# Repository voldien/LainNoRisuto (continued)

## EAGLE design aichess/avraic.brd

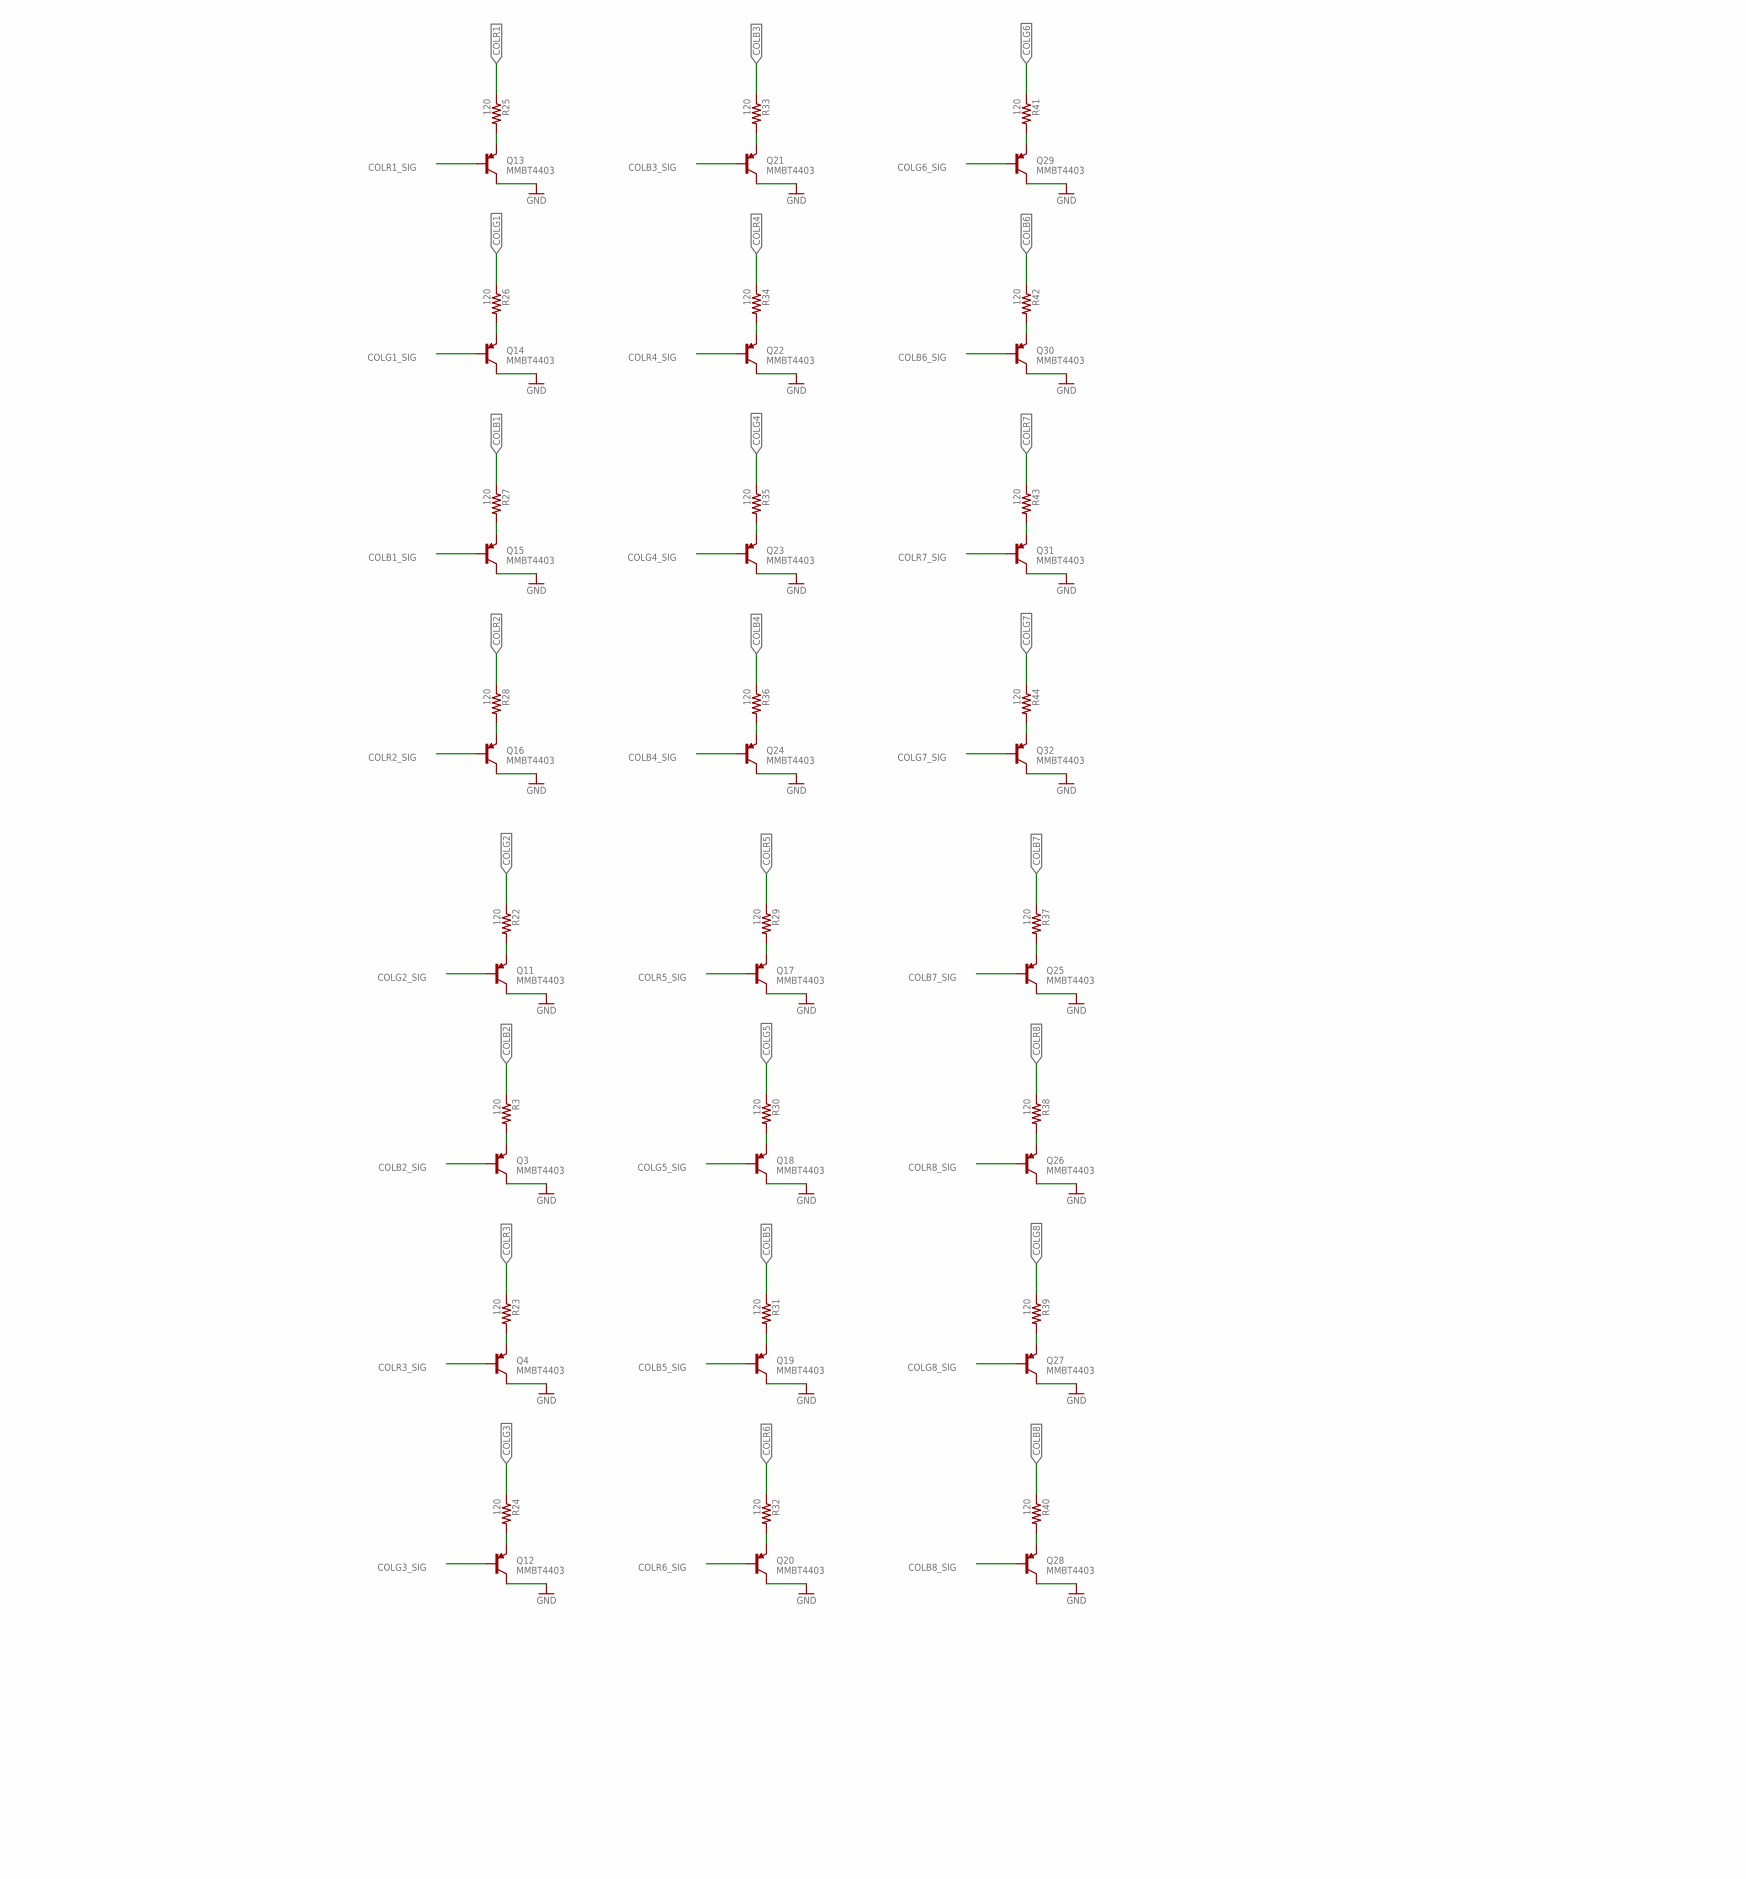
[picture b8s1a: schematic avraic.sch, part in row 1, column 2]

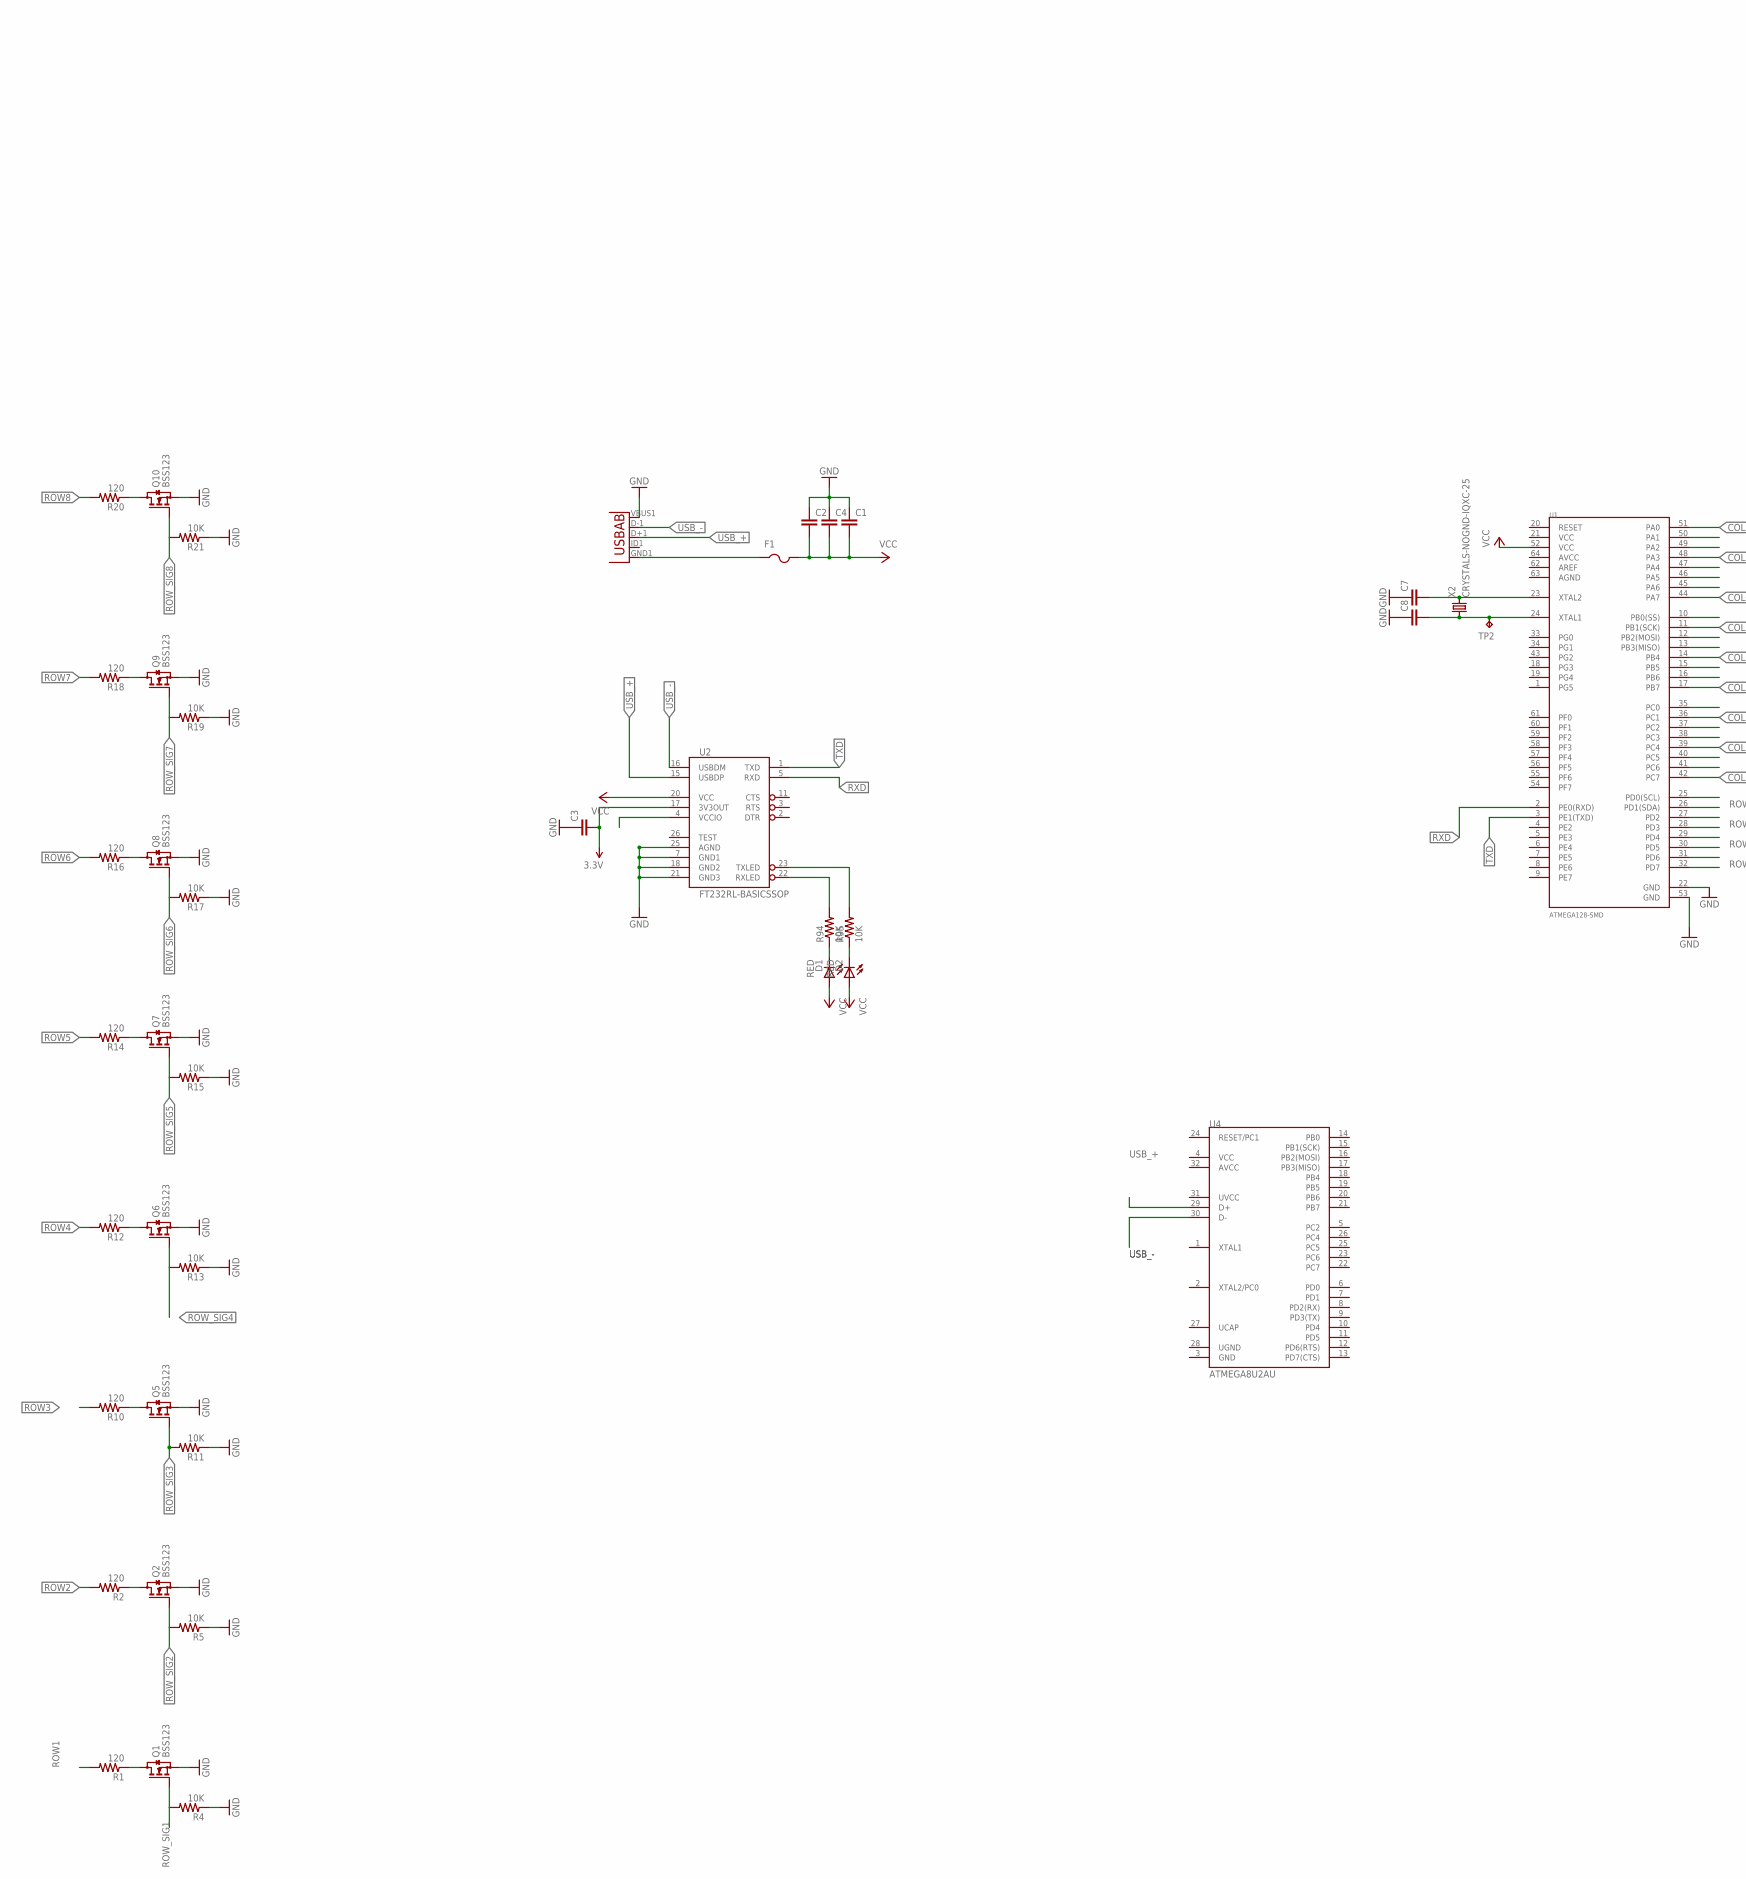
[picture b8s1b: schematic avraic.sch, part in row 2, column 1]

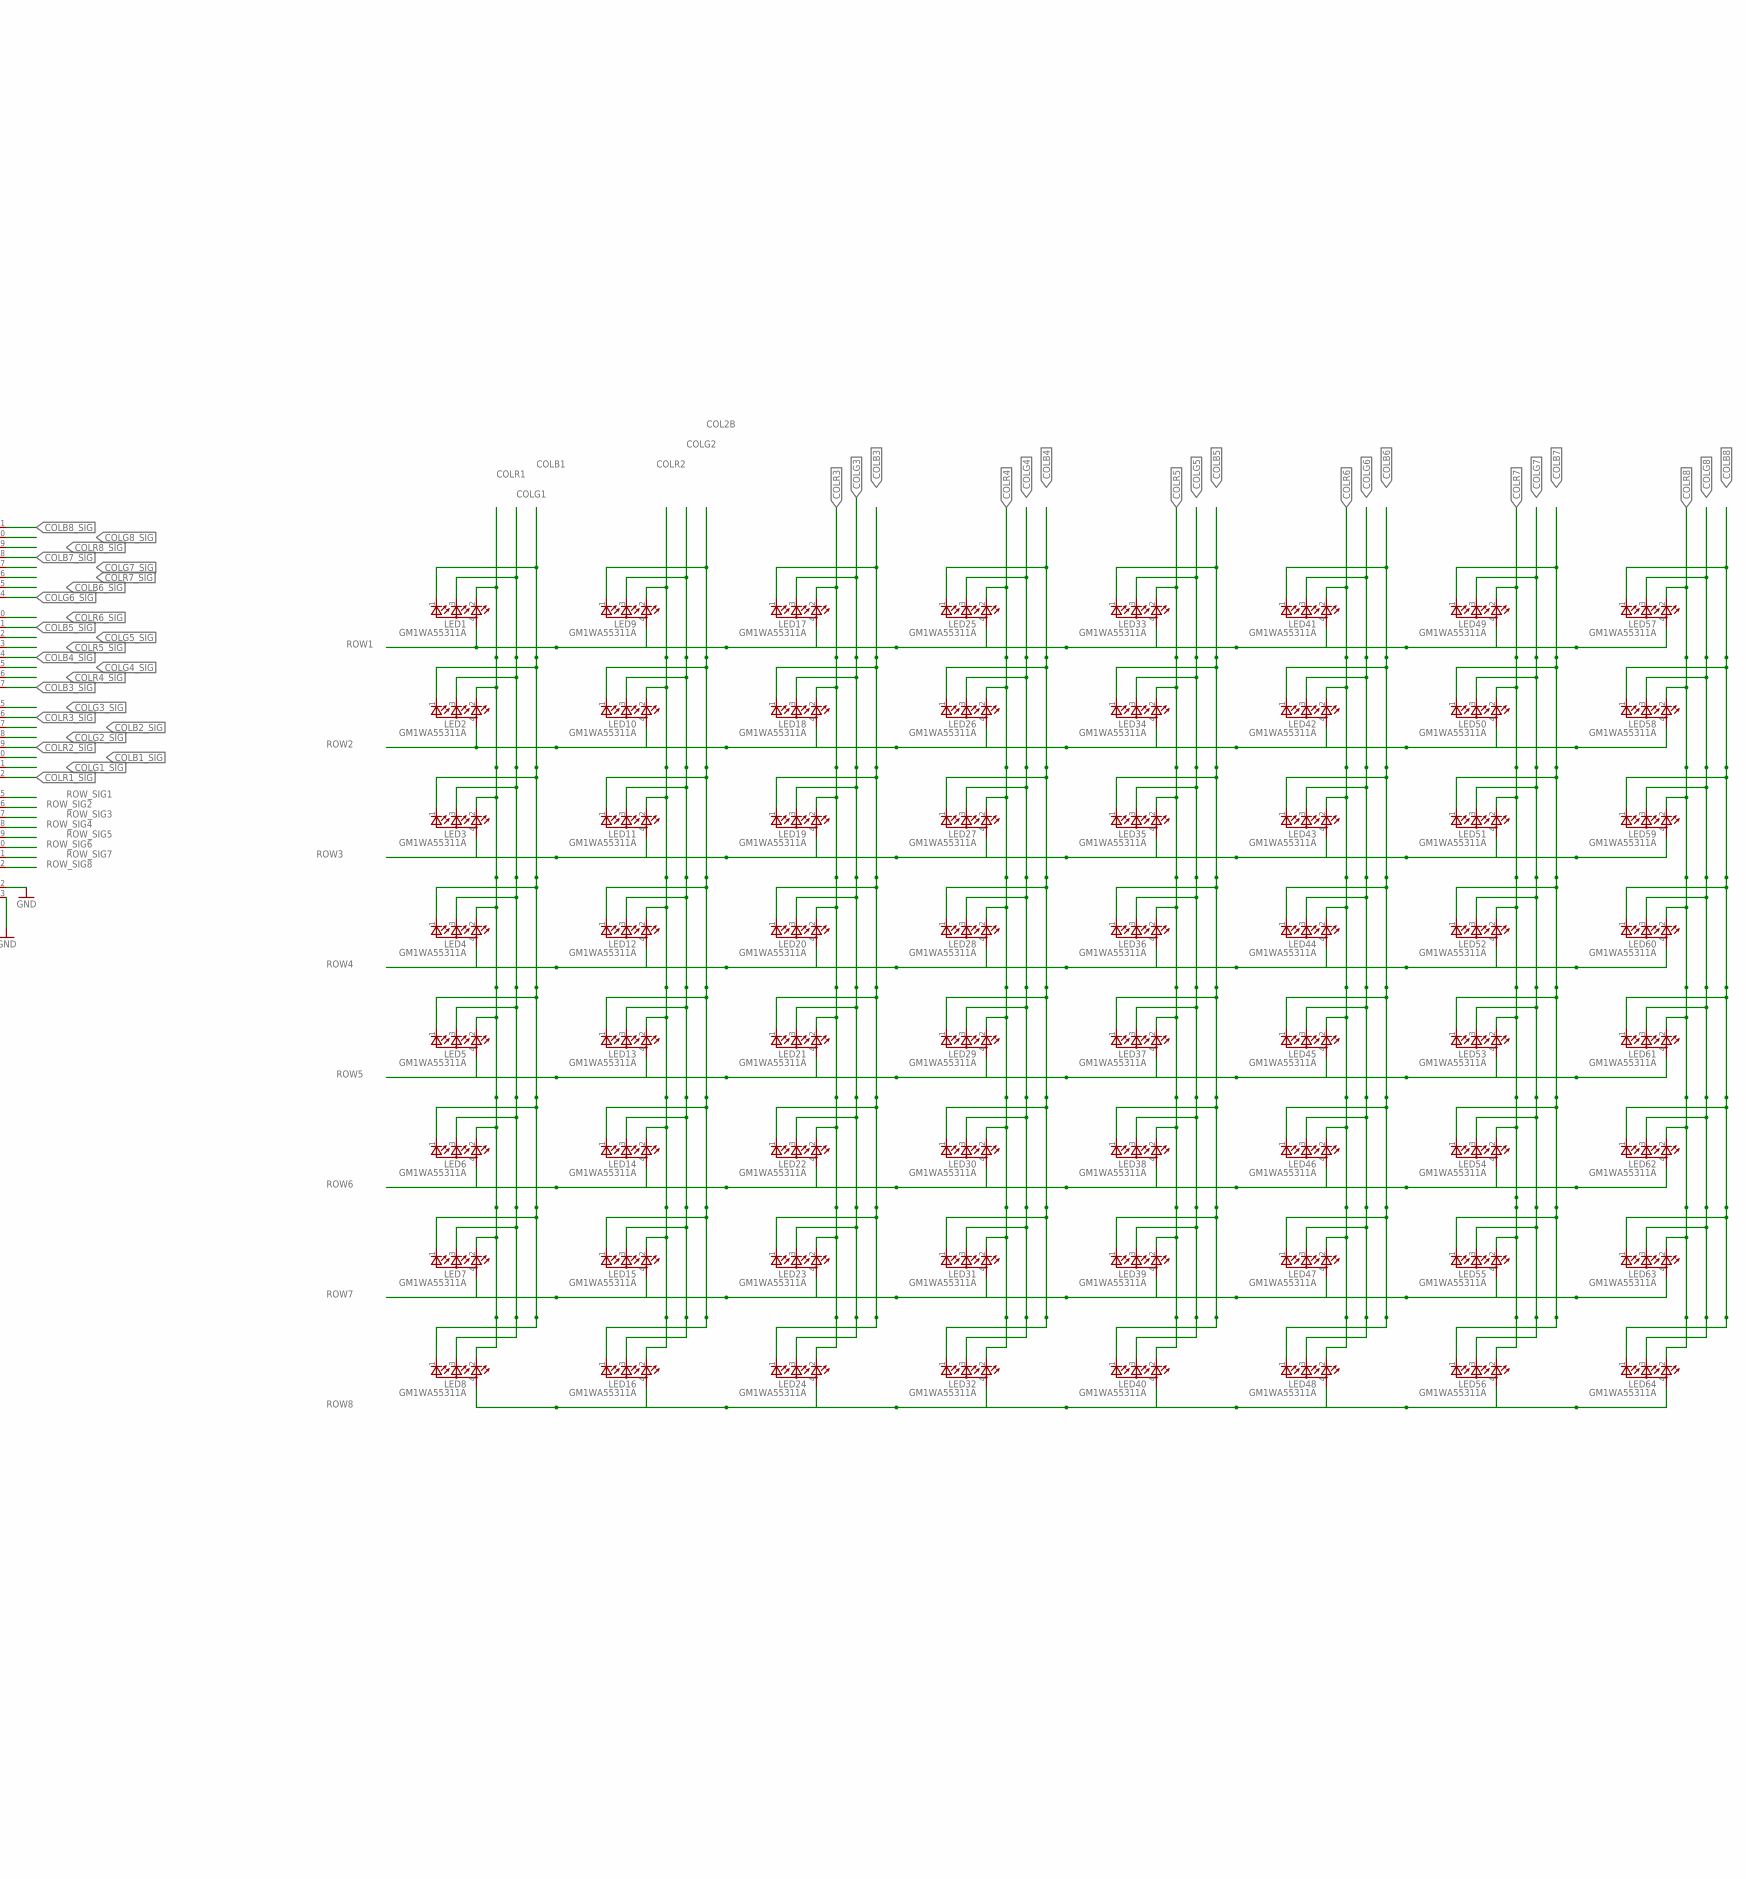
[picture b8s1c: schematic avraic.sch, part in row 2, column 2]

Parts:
C1, C2, C4: C-EUC0201; C0201
C3, C7, C8: C-EUC0402K; C0402K
D1, D2: RED; CHIP-LED0603
F1: PTCFUSE-1206; R1206
LED1, LED2, LED3, LED4, LED5, LED6, LED7, LED8, LED9, LED10, LED11, LED12, LED13, LED14, LED15, LED16, LED17, LED18, LED19, LED20, LED21, LED22, LED23, LED24, LED25, LED26, LED27, LED28, LED29, LED30, LED31, LED32, LED33, LED34, LED35, LED36, LED37, LED38, LED39, LED40, LED41, LED42, LED43, LED44, LED45, LED46, LED47, LED48, LED49, LED50, LED51, LED52, LED53, LED54, LED55, LED56, LED57, LED58, LED59, LED60, LED61, LED62, LED63, LED64: GM1WA55311A
Q1, Q2, Q5, Q6, Q7, Q8, Q9, Q10: BSS123; SOT23
Q3, Q4, Q11, Q12, Q13, Q14, Q15, Q16, Q17, Q18, Q19, Q20, Q21, Q22, Q23, Q24, Q25, Q26, Q27, Q28, Q29, Q30, Q31, Q32: MMBT4403; SOT23-3
R1, R2, R10, R12, R14, R16, R18, R20, R24, R25, R30, R31, R32: 120; 0603-RES
R3, R22, R23, R26, R27, R28, R29, R33, R34, R35, R36, R37, R38, R39, R40, R41, R42, R43, R44: 120; MINI_MELF-0102R
R4, R5, R11, R13, R15, R17, R19, R21, R94, R95: 10K; 0603-RES
TP2: TPB1,27; B1,27
U1: ATMEGA128-SMD; TQFP64_14X14MM
U2: FT232RL-BASICSSOP; SSOP28DB
U3: USB""; USB-MICRO-SMD
U4: ATMEGA8U2AU; TQFP32-08
X2: CRYSTALS-NOGND-IQXC-25; 2.0X1.2-2PAD

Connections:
3.3V: C3.2, U2.17 (3V3OUT)
COL2B: LED9.1 (CGREEN), LED10.1 (CGREEN), LED11.1 (CGREEN), LED12.1 (CGREEN), LED13.1 (CGREEN), LED14.1 (CGREEN), LED15.1 (CGREEN), LED16.1 (CGREEN)
COLB1: LED1.1 (CGREEN), LED2.1 (CGREEN), LED3.1 (CGREEN), LED4.1 (CGREEN), LED5.1 (CGREEN), LED6.1 (CGREEN), LED7.1 (CGREEN), LED8.1 (CGREEN), R27.1
COLB1_SIG: Q15.1 (B), U1.40 (PC5)
COLB2: R3.1
COLB2_SIG: Q3.1 (B), U1.37 (PC2)
COLB3: LED17.1 (CGREEN), LED18.1 (CGREEN), LED19.1 (CGREEN), LED20.1 (CGREEN), LED21.1 (CGREEN), LED22.1 (CGREEN), LED23.1 (CGREEN), LED24.1 (CGREEN), R33.1
COLB3_SIG: Q21.1 (B), U1.17 (PB7)
COLB4: LED25.1 (CGREEN), LED26.1 (CGREEN), LED27.1 (CGREEN), LED28.1 (CGREEN), LED29.1 (CGREEN), LED30.1 (CGREEN), LED31.1 (CGREEN), LED32.1 (CGREEN), R36.1
COLB4_SIG: Q24.1 (B), U1.14 (PB4)
COLB5: LED33.1 (CGREEN), LED34.1 (CGREEN), LED35.1 (CGREEN), LED36.1 (CGREEN), LED37.1 (CGREEN), LED38.1 (CGREEN), LED39.1 (CGREEN), LED40.1 (CGREEN), R31.1
COLB5_SIG: Q19.1 (B), U1.11 (PB1(SCK))
COLB6: LED41.1 (CGREEN), LED42.1 (CGREEN), LED43.1 (CGREEN), LED44.1 (CGREEN), LED45.1 (CGREEN), LED46.1 (CGREEN), LED47.1 (CGREEN), LED48.1 (CGREEN), R42.1
COLB6_SIG: Q30.1 (B), U1.45 (PA6)
COLB7: LED49.1 (CGREEN), LED50.1 (CGREEN), LED51.1 (CGREEN), LED52.1 (CGREEN), LED53.1 (CGREEN), LED54.1 (CGREEN), LED55.1 (CGREEN), LED56.1 (CGREEN), R37.1
COLB7_SIG: Q25.1 (B), U1.48 (PA3)
COLB8: LED57.1 (CGREEN), LED58.1 (CGREEN), LED59.1 (CGREEN), LED60.1 (CGREEN), LED61.1 (CGREEN), LED62.1 (CGREEN), LED63.1 (CGREEN), LED64.1 (CGREEN), R40.1
COLB8_SIG: Q28.1 (B), U1.51 (PA0)
COLG1: LED1.3 (CBLUE), LED2.3 (CBLUE), LED3.3 (CBLUE), LED4.3 (CBLUE), LED5.3 (CBLUE), LED6.3 (CBLUE), LED7.3 (CBLUE), LED8.3 (CBLUE), R26.1
COLG1_SIG: Q14.1 (B), U1.41 (PC6)
COLG2: LED9.3 (CBLUE), LED10.3 (CBLUE), LED11.3 (CBLUE), LED12.3 (CBLUE), LED13.3 (CBLUE), LED14.3 (CBLUE), LED15.3 (CBLUE), LED16.3 (CBLUE), R22.1
COLG2_SIG: Q11.1 (B), U1.38 (PC3)
COLG3: LED17.3 (CBLUE), LED18.3 (CBLUE), LED19.3 (CBLUE), LED20.3 (CBLUE), LED21.3 (CBLUE), LED22.3 (CBLUE), LED23.3 (CBLUE), LED24.3 (CBLUE), R24.1
COLG3_SIG: Q12.1 (B), U1.35 (PC0)
COLG4: LED25.3 (CBLUE), LED26.3 (CBLUE), LED27.3 (CBLUE), LED28.3 (CBLUE), LED29.3 (CBLUE), LED30.3 (CBLUE), LED31.3 (CBLUE), LED32.3 (CBLUE), R35.1
COLG4_SIG: Q23.1 (B), U1.15 (PB5)
COLG5: LED33.3 (CBLUE), LED34.3 (CBLUE), LED35.3 (CBLUE), LED36.3 (CBLUE), LED37.3 (CBLUE), LED38.3 (CBLUE), LED39.3 (CBLUE), LED40.3 (CBLUE), R30.1
COLG5_SIG: Q18.1 (B), U1.12 (PB2(MOSI))
COLG6: LED41.3 (CBLUE), LED42.3 (CBLUE), LED43.3 (CBLUE), LED44.3 (CBLUE), LED45.3 (CBLUE), LED46.3 (CBLUE), LED47.3 (CBLUE), LED48.3 (CBLUE), R41.1
COLG6_SIG: Q29.1 (B), U1.44 (PA7)
COLG7: LED49.3 (CBLUE), LED50.3 (CBLUE), LED51.3 (CBLUE), LED52.3 (CBLUE), LED53.3 (CBLUE), LED54.3 (CBLUE), LED55.3 (CBLUE), LED56.3 (CBLUE), R44.1
COLG7_SIG: Q32.1 (B), U1.47 (PA4)
COLG8: LED57.3 (CBLUE), LED58.3 (CBLUE), LED59.3 (CBLUE), LED60.3 (CBLUE), LED61.3 (CBLUE), LED62.3 (CBLUE), LED63.3 (CBLUE), LED64.3 (CBLUE), R39.1
COLG8_SIG: Q27.1 (B), U1.50 (PA1)
COLR1: LED1.2 (CRED), LED2.2 (CRED), LED3.2 (CRED), LED4.2 (CRED), LED5.2 (CRED), LED6.2 (CRED), LED7.2 (CRED), LED8.2 (CRED), R25.1
COLR1_SIG: Q13.1 (B), U1.42 (PC7)
COLR2: LED9.2 (CRED), LED10.2 (CRED), LED11.2 (CRED), LED12.2 (CRED), LED13.2 (CRED), LED14.2 (CRED), LED15.2 (CRED), LED16.2 (CRED), R28.1
COLR2_SIG: Q16.1 (B), U1.39 (PC4)
COLR3: LED17.2 (CRED), LED18.2 (CRED), LED19.2 (CRED), LED20.2 (CRED), LED21.2 (CRED), LED22.2 (CRED), LED23.2 (CRED), LED24.2 (CRED), R23.1
COLR3_SIG: Q4.1 (B), U1.36 (PC1)
COLR4: LED25.2 (CRED), LED26.2 (CRED), LED27.2 (CRED), LED28.2 (CRED), LED29.2 (CRED), LED30.2 (CRED), LED31.2 (CRED), LED32.2 (CRED), R34.1
COLR4_SIG: Q22.1 (B), U1.16 (PB6)
COLR5: LED33.2 (CRED), LED34.2 (CRED), LED35.2 (CRED), LED36.2 (CRED), LED37.2 (CRED), LED38.2 (CRED), LED39.2 (CRED), LED40.2 (CRED), R29.1
COLR5_SIG: Q17.1 (B), U1.13 (PB3(MISO))
COLR6: LED41.2 (CRED), LED42.2 (CRED), LED43.2 (CRED), LED44.2 (CRED), LED45.2 (CRED), LED46.2 (CRED), LED47.2 (CRED), LED48.2 (CRED), R32.1
COLR6_SIG: Q20.1 (B), U1.10 (PB0(SS))
COLR7: LED49.2 (CRED), LED50.2 (CRED), LED51.2 (CRED), LED52.2 (CRED), LED53.2 (CRED), LED54.2 (CRED), LED55.2 (CRED), LED56.2 (CRED), R43.1
COLR7_SIG: Q31.1 (B), U1.46 (PA5)
COLR8: LED57.2 (CRED), LED58.2 (CRED), LED59.2 (CRED), LED60.2 (CRED), LED61.2 (CRED), LED62.2 (CRED), LED63.2 (CRED), LED64.2 (CRED), R38.1
COLR8_SIG: Q26.1 (B), U1.49 (PA2)
GND: C1.1, C2.1, C3.1, C4.1, C7.1, C8.1, Q1.2 (S), Q2.2 (S), Q3.3 (C), Q4.3 (C), Q5.2 (S), Q6.2 (S), Q7.2 (S), Q8.2 (S), Q9.2 (S), Q10.2 (S), Q11.3 (C), Q12.3 (C), Q13.3 (C), Q14.3 (C), Q15.3 (C), Q16.3 (C), Q17.3 (C), Q18.3 (C), Q19.3 (C), Q20.3 (C), Q21.3 (C), Q22.3 (C), Q23.3 (C), Q24.3 (C), Q25.3 (C), Q26.3 (C), Q27.3 (C), Q28.3 (C), Q29.3 (C), Q30.3 (C), Q31.3 (C), Q32.3 (C), R4.1, R5.1, R11.1, R13.1, R15.1, R17.1, R19.1, R21.1, U1.22 (GND), U1.53 (GND), U2.7 (GND1), U2.18 (GND2), U2.21 (GND3), U2.25 (AGND), U3.VBUS1 (VBUS)
unnamed: F1.1, U3.GND1 (GND)
unnamed: Q11.2 (E), R22.2
unnamed: Q1.3 (D), R1.1
unnamed: Q3.2 (E), R3.2
unnamed: Q4.2 (E), R23.2
unnamed: Q2.3 (D), R2.1
unnamed: D1.C, R94.1
unnamed: Q12.2 (E), R24.2
unnamed: D2.C, R95.1
unnamed: C7.2, U1.23 (XTAL2), X2.2
unnamed: C8.2, TP2.TP, U1.24 (XTAL1), X2.1
unnamed: Q13.2 (E), R25.2
unnamed: Q14.2 (E), R26.2
unnamed: Q15.2 (E), R27.2
unnamed: Q16.2 (E), R28.2
unnamed: Q17.2 (E), R29.2
unnamed: Q18.2 (E), R30.2
unnamed: Q19.2 (E), R31.2
unnamed: Q20.2 (E), R32.2
unnamed: Q21.2 (E), R33.2
unnamed: Q22.2 (E), R34.2
unnamed: Q23.2 (E), R35.2
unnamed: Q24.2 (E), R36.2
unnamed: Q25.2 (E), R37.2
unnamed: Q26.2 (E), R38.2
unnamed: Q27.2 (E), R39.2
unnamed: Q28.2 (E), R40.2
unnamed: Q29.2 (E), R41.2
unnamed: Q30.2 (E), R42.2
unnamed: Q31.2 (E), R43.2
unnamed: Q32.2 (E), R44.2
unnamed: Q5.3 (D), R10.1
unnamed: Q6.3 (D), R12.1
unnamed: Q7.3 (D), R14.1
unnamed: Q8.3 (D), R16.1
unnamed: Q9.3 (D), R18.1
unnamed: Q10.3 (D), R20.1
unnamed: R95.2, U2.23 (TXLED)
unnamed: R94.2, U2.22 (RXLED)
ROW1: LED1.4 (A), LED9.4 (A), LED17.4 (A), LED25.4 (A), LED33.4 (A), LED41.4 (A), LED49.4 (A), LED57.4 (A), R1.2
ROW2: LED2.4 (A), LED10.4 (A), LED18.4 (A), LED26.4 (A), LED34.4 (A), LED42.4 (A), LED50.4 (A), LED58.4 (A), R2.2
ROW3: LED3.4 (A), LED11.4 (A), LED19.4 (A), LED27.4 (A), LED35.4 (A), LED43.4 (A), LED51.4 (A), LED59.4 (A), R10.2
ROW4: LED4.4 (A), LED12.4 (A), LED20.4 (A), LED28.4 (A), LED36.4 (A), LED44.4 (A), LED52.4 (A), LED60.4 (A), R12.2
ROW5: LED5.4 (A), LED13.4 (A), LED21.4 (A), LED29.4 (A), LED37.4 (A), LED45.4 (A), LED53.4 (A), LED61.4 (A), R14.2
ROW6: LED6.4 (A), LED14.4 (A), LED22.4 (A), LED30.4 (A), LED38.4 (A), LED46.4 (A), LED54.4 (A), LED62.4 (A), R16.2
ROW7: LED7.4 (A), LED15.4 (A), LED23.4 (A), LED31.4 (A), LED39.4 (A), LED47.4 (A), LED55.4 (A), LED63.4 (A), R18.2
ROW8: LED8.4 (A), LED16.4 (A), LED24.4 (A), LED32.4 (A), LED40.4 (A), LED48.4 (A), LED56.4 (A), LED64.4 (A), R20.2
ROW_SIG1: Q1.1 (G), R4.2, U1.25 (PD0(SCL))
ROW_SIG2: Q2.1 (G), R5.2, U1.26 (PD1(SDA))
ROW_SIG3: Q5.1 (G), R11.2, U1.27 (PD2)
ROW_SIG4: Q6.1 (G), R13.2, U1.28 (PD3)
ROW_SIG5: Q7.1 (G), R15.2, U1.29 (PD4)
ROW_SIG6: Q8.1 (G), R17.2, U1.30 (PD5)
ROW_SIG7: Q9.1 (G), R19.2, U1.31 (PD6)
ROW_SIG8: Q10.1 (G), R21.2, U1.32 (PD7)
RXD: U1.2 (PE0(RXD)), U2.5 (RXD)
TXD: U1.3 (PE1(TXD)), U2.1 (TXD)
USB_+: U2.15 (USBDP), U3.D+1 (D+), U4.29 (D+)
USB_-: U2.16 (USBDM), U3.D-1 (D-), U4.30 (D-)
VCC: C1.2, C2.2, C4.2, D1.A, D2.A, F1.2, U1.52 (VCC), U2.20 (VCC)

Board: 2 copper layers, 153 parts (56 on the bottom side), 110 nets, no tracks yet.

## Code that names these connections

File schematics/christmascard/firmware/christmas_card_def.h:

#ifndef _CHRISTMAS_CARD_DEF_H_
#define _CHRISTMAS_CARD_DEF_H_ 1

/**
 * Push Button Registers and Pin.
 * Reset Button
 */
#define PUSH_BUTTON0_REG PORTB
#define PUSH_BUTTON0_DREG DDRB
#define PUSH_BUTTON0_IREG PINB
#define PUSH_BUTTON0_PIN PB0

/**
 * Push Button Registers and Pin
 * Next Button
 */
#define PUSH_BUTTON1_REG PORTA
#define PUSH_BUTTON1_DREG DDRA
#define PUSH_BUTTON1_IREG PINA
#define PUSH_BUTTON1_PIN PA1

/**
 * Shift Registers Output Enabled (SNx4HC595)
 * Pin and Registers.
 */
#define SHIFT_OE_REG PORTA /*		*/
#define SHIFT_OE_DREG DDRA /*		*/
#define SHIFT_OE_PIN PA0   /*		*/
#define SHIFT_OE_PWM_REG OCR0A

/**
 * Shift Register Shift Clock Pin (SNx4HC595)
 * and Registers  (RCLK)
 */
#define SHIFT_RCLK_REG PORTB /*	 	*/
#define SHIFT_RCLK_DREG DDRB /*	 	*/
#define SHIFT_RCLK_PIN PB1	 /*	 	*/

/**
 * Shift Registers Serial Data Pin (SNx4HC595)
 * and Registers
 */
#define SHIFT_DIO_REG PORTB /*		*/
#define SHIFT_DIO_DREG DDRB /*		*/
#define SHIFT_DIO_PIN PB2	/*		*/

/**
 * Shift Registers Latch (Flush Data to Output) Pin (SNx4HC595)
 * and Register  (SRCLR)
 */
#define SHIFT_LATCH_REG PORTB
#define SHIFT_LATCH_DREG DDRB
#define SHIFT_LATCH_PIN PB3 /*	Shift clock.	*/

/**
 *
 */
#define WS2811_DREG DDRA
#define WS2811_REG PORTA
#define WS2811_PIN PA3

#define WS2811_IN (1 << WS2811_PIN)

#endif

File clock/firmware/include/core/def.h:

/**

    Copyright (C) 2018  Valdemar Lindberg

    This program is free software: you can redistribute it and/or modify
    it under the terms of the GNU General Public License as published by
    the Free Software Foundation, either version 3 of the License, or
    (at your option) any later version.

    This program is distributed in the hope that it will be useful,
    but WITHOUT ANY WARRANTY; without even the implied warranty of
    MERCHANTABILITY or FITNESS FOR A PARTICULAR PURPOSE.  See the
    GNU General Public License for more details.

    You should have received a copy of the GNU General Public License
    along with this program.  If not, see <http://www.gnu.org/licenses/>.

*/
#ifndef _AVR_CLOCK_DEF_H_
#define _AVR_CLOCK_DEF_H_ 1
#include<avr/io.h>

/*	Set default frequency.	*/
#ifndef F_SCL
	#define F_SCL 100000UL /* SCL frequency	*/
#endif

/*	Set default baud rate.	*/
#ifndef BAUD
	#define BAUD 9600
#endif

#if defined(__AVR_ATmega328P__)
	#define SPIPORTS ( 1<<PD0) | (1 << PD1);
	#define I2CPORTS (1<<PD0) | (1 << PD1);
	#define UARTPORTS (1 << PD0) | (1 << PD1);
	#define BUTTONPORTS (1<<PD0) | (1 << PD1);
	#define pinclk PB0
	#define pindio PB1
	#define DIOPIN PINB
	#define DIODDR DDRB
	#define DIOPORT PORTB
#endif

#endif

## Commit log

2021-05-01 Config files
2021-05-01 Added tiny blink init source code
2021-05-01 Added init christmas card source code
2021-05-01 Added christmas schematic and pcb board
2021-05-01 Added atdb
2021-05-01 atdb pcb and schematic
2021-05-01 Added schematic and board
2021-05-01 Added root cmake
2021-05-01 Added
2021-05-01 Added readme and license file
2021-05-01 Add more source files
2021-05-01 Addded cmake module for handle avr-gcc with CMake
2021-05-01 Added gerber files
2021-05-01 Added schematic and board layout
2021-05-01 Added image of atdb
2021-05-02 Added layout
2021-05-03 Clock init souce files
2021-05-03 init source files
2021-05-12 Added board layout
2021-05-12 Minor update
2021-05-12 Init readme
2021-08-14 Minor
2021-08-31 Added init LED matrix
2021-09-01 Updated schematic
2021-09-03 Improved annotations and board layout
2021-09-04 Updated layout
2021-09-04 Updated layout grid
2021-09-04 Setup LED matrix
2021-09-05 Updated schematic and layout
2021-09-17 Updated minor
2021-12-22 Init
2022-01-06 Improved layout and schematic
2022-01-06 Init game console design
2022-04-12 Code formated
2023-01-20 Added init christmas card version 2.0
2023-04-06 Added init christmas card version 2 schematic and layout
2023-04-06 removed, replaced
2023-04-06 Added init source code, copied from the christmas card V1
2023-04-06 Added init source code for LED Clock matrix
2023-04-07 Added readme and removed file
2023-05-29 Added kicad git ignore
2023-05-29 Added init kicad source files
2023-05-29 Added init WIP game console firmware code
2023-05-30 Minor improvements
2025-05-21 Improved logic and other changes
2025-05-21 Updated git ignore
2025-05-21 Added AVR cmake config file
2025-05-21 Improved signal and other minor improvements
2025-05-22 Added pin interrupt, timer overflow interrupt and other changes and improvements
2025-05-22 Improvement and other changes
2025-05-23 Improved push button and other changes
2025-05-24 Improved code and minor doc
2025-05-24 Updated schematic and board layout
2025-05-25 Fixed RCLK trace missing issue
2025-05-28 Relocated files, removed unused files, updated christmas and clock board and other changes
2025-06-08 Init source code
2025-06-11 Improvement and changes
2025-06-11 Code cleanup and other changes
2025-07-05 Minor board fixes and other changes
2025-07-21 Removed unused files, update board, code and other changes
2025-07-29 Added LED Matrix
2025-07-31 Minor fixes and cleanup
2025-08-07 Fixed clock prescalar, and minor fixes
2025-08-14 Improvement, fixes and other changes
2026-01-05 Relocated files and minor changes
2026-01-31 Updated Gerber
